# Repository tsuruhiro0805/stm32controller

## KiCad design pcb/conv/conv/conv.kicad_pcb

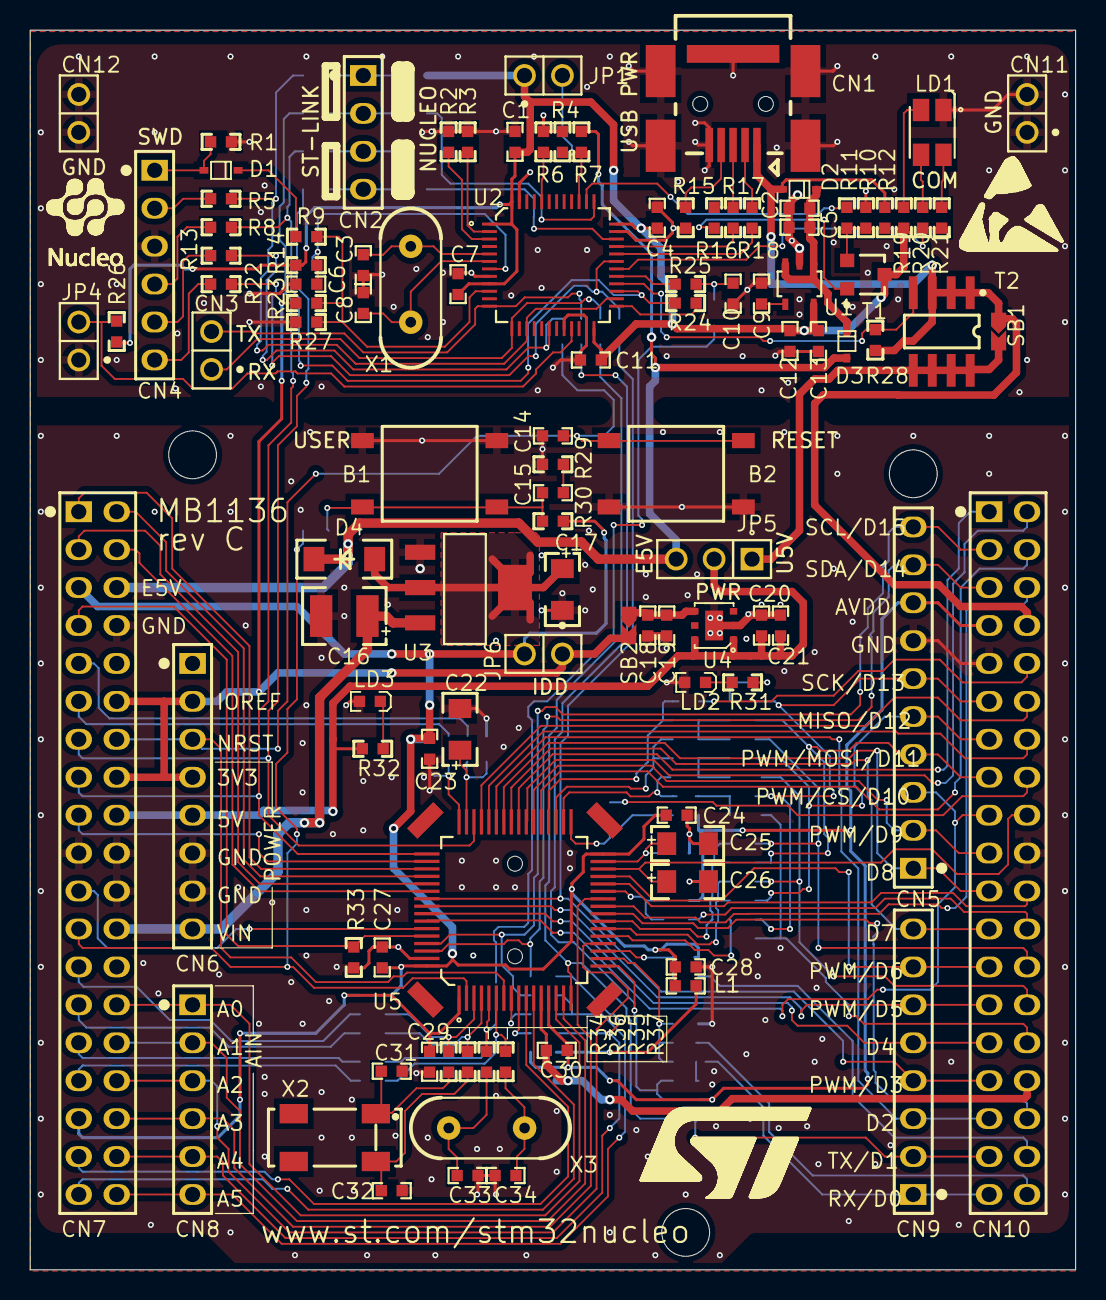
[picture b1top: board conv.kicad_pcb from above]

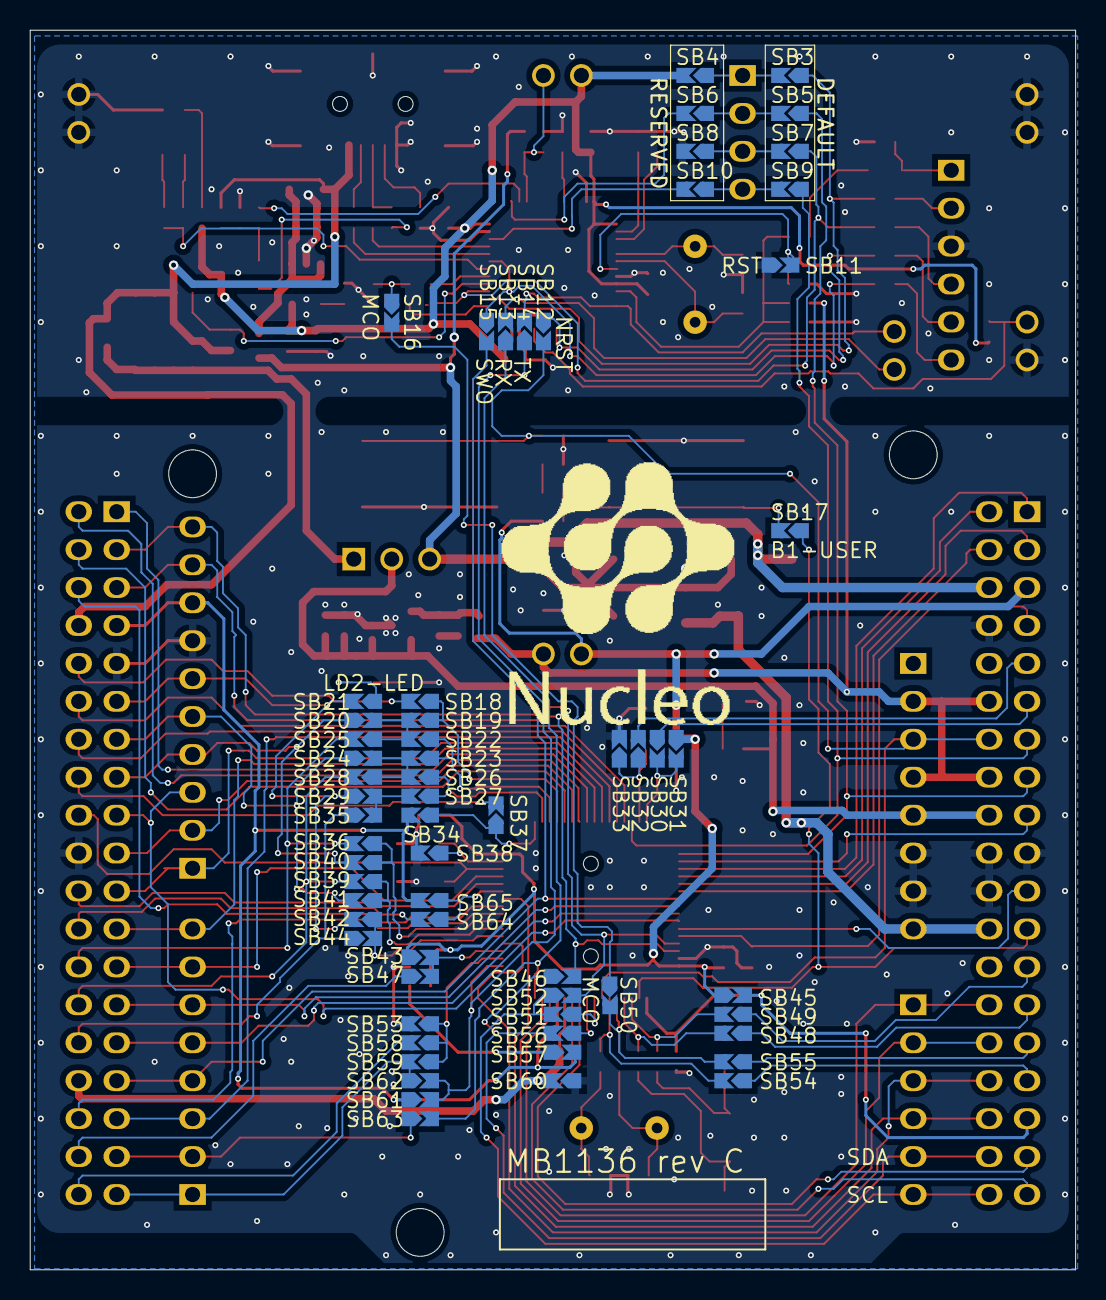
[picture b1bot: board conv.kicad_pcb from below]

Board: 2 copper layers, 70.0 x 83.0 mm, 176 parts (64 on the bottom side), 152 nets.

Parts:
B1: USER (Blue); PB10
B2: TD-0341 [RESET/Black]; PB10
C1, C4, C5, C6, C7, C11, C12, C14, C15, C19, C20, C23, C24, C27, C28, C30: 100nF; 0603C
C2, C13, C18, C21, C29: 1uF_X5R_0603; 0603C
C3, C8, C10: 20pF; 0603C
C9: 10nF_X7R_0603; 0603C
C16: 10uF(25V); TAN-B
C17: 10uF; TAN-A
C22, C25, C26: 2.2uF; TAN-A
C31, C32: 10pF[N/A]; 0603C
C33, C34: 20pF[N/A]; 0603C
CN1: 5075BMR-05-SM; USB-MINI-B-SMD
CN2: Header 4; 1*4
CN3, CN11, CN12: SIP2/2.54
CN4: Header 6X1; 1*6P
CN5: Header 10X1_Female; 1*10P_FEMALE
CN6, CN9: Header 8X1_Female; 1*8P_FEMALE
CN7, CN10: Header 19X2; 2*19P
CN8: Header 6X1_Female; 1*6P_FEMALE
D1, D2, D3: BAT60JFILM; SOD323/A
D4: STPS2L30A; SMA
Designator1: Comment; NUCLEO_black 0.5cm
Designator2: Comment; LOGO ESD
Designator4: Comment; NUCLEO_black 2cm
Designator22: Comment; ST_LOGO_10mm
JP1, JP4, JP6: SIP2/2.54
JP5: SIP3
L1: BEAD; 0603L
LD1: LD_BICOLOR_CMS; HSMF-A201
LD2: Green; 0603D
LD3: RED; 0603D
R1, R2, R3, R12, R26, R33: 10K; 0603R
R4, R23, R27, R28, R30: 4K7; 0603R
R5, R8, R13, R22: 22; 0603R
R6, R14, R15: 100K; 0603R
R7: 2K7; 0603R
R9, R11, R20, R21, R24, R25, R29: 100; 0603R
R10: 36K; 0603R
R16: 1K5; 0603R
R17, R18, R19: 0; 0603R
R31: 510; 0603R
R32: 1K; 0603R
R34, R35, R36, R37: [N/A]; 0603R
SB1, SB2, SB3, SB4, SB5, SB6, SB7, SB8, SB9, SB10, SB11, SB12, SB13, SB14, SB15, SB16, SB17, SB18, SB19, SB20, SB21, SB22, SB23, SB24, SB25, SB26, SB27, SB28, SB29, SB30, SB31, SB32, SB33, SB34, SB35, SB36, SB37, SB38, SB39, SB40, SB41, SB42, SB43, SB44, SB45, SB46, SB47, SB48, SB49, SB50, SB51, SB52, SB53, SB54, SB55, SB56, SB57, SB58, SB59, SB60, SB61, SB62, SB63, SB64, SB65: Circuit Breaker; JP2_SMD
T1: 9013; SOT-23
T2: STS7PF30L; SO8
U1: LD3985M33R; SOT-23-5L
U2: STM32F103CBT6; QFP48 7X7
U3: LD1117S50TR; SOT-223
U4: LD39050PU33R; DFN6(3X3)
U5: MCU_LQFP64; LQFP64
X1: 8MHz(12pF); XTAL1
X2: 32.768K[N/A]; XTAL_4SM_8X3R8
X3: 8MHz(16pF)[N/A]; XTAL1

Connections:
+3V3: CN6.2, CN6.4, CN7.12, CN7.16, JP6.1, R23.1, SB2.2
+3V3_ST_LINK: C1.2, C4.2, C7.2, C11.2, C12.2, C13.1, JP1.1, R14.2, R19.2, R26.1, SB4.2, T1.3, U1.5, U2.1, U2.9, U2.24, U2.36, U2.48
+5V: C20.2, C21.1, CN6.5, CN7.18, JP5.2, R32.2, U4.1, U4.6
AGND: C30.2, CN10.32, SB60.2, U5.12
AIN_1: R9.2, R23.2, R27.2, U2.10
AVDD: C30.1, CN5.8, CN10.7, SB34.2, SB57.2, SB61.1, SB65.2, U5.13
BOOT0: CN7.7, R33.1, U5.60
E5V: CN7.6, D3.1, D4.2, JP5.3, R7.1
GND: B1.1, B1.4, B2.1, B2.4, C1.1, C2.1, C3.2, C4.1, C5.1, C6.1, C7.1, C8.2, C9.1, C10.2, C11.1, C12.1, C13.2, C14.1, C16.2, C17.2, C18.2, C19.1, C20.1, C21.2, C22.2, C23.2, C24.2, C25.2, C26.2, C27.2, C28.2, C29.2, C31.2, C32.2, C33.2, C34.2, CN1.5, CN1.6, CN4.3, CN5.7, CN6.6, CN6.7, CN7.8, CN7.19, CN7.20, CN7.22, CN10.9, CN10.20, CN11.1, CN11.2, CN12.1, CN12.2, JP4.1, LD1.1, LD2.2, LD3.2, R1.2, R2.1, R3.1, R4.2, R6.1, R10.1, R15.2, R27.1, R29.1, R33.2, SB8.2, SB11.1, SB33.2, SB38.2, SB53.2, SB60.1, U1.2, U2.8, U2.20, U2.23, U2.35, U2.47, U3.1, U4.0, U4.2, U5.63
LED_STLINK: R20.1, R21.1, U2.30
MCO: SB16.2, SB50.1
NRST: B2.2, B2.3, C14.2, CN6.3, CN7.14, SB12.2, U5.7
NetB1_2: B1.2, B1.3, C15.2, R30.1, SB17.2
NetC2_2: C2.2, C5.2, D2.2, D3.2, U1.1, U1.3
NetC9_2: C9.2, U1.4
NetC10_1: C10.1, R25.2, SB16.1
NetC15_1: C15.1, R29.2
NetC17_1: C17.1, D4.1, U3.2, U3.4
NetC18_1: C18.1, C19.2, SB2.1, U4.4
NetC22_1: C22.1, SB32.1, SB33.1, U5.47
NetC25_1: C25.1, SB38.1, U5.31
NetC31_1: C31.1, R34.1, X2.1
NetC32_1: C32.1, R36.1, X2.4
NetC33_1: C33.1, R35.2, X3.2
NetC34_1: C34.1, R37.2, X3.1
NetCN1_2: CN1.2, R18.1
NetCN1_3: CN1.3, R16.1, R17.1
NetCN1_4: CN1.4, R15.1
NetCN2_1: CN2.1, SB3.2, SB4.1
NetCN2_2: CN2.2, SB5.2, SB6.1
NetCN2_3: CN2.3, SB7.2, SB8.1
NetCN2_4: CN2.4, SB9.2, SB10.1
NetCN4_1: CN4.1, D1.1, R1.1
NetCN4_2: CN4.2, R5.1
NetCN4_4: CN4.4, R8.1
NetCN4_5: CN4.5, R13.1
NetCN4_6: CN4.6, R22.1
NetCN5_4: CN5.4, CN10.15, SB20.1, SB40.2
NetCN5_5: CN5.5, CN10.13, SB24.1, SB41.2
NetCN5_6: CN5.6, CN10.11, SB21.2, SB29.1, SB42.2
NetCN7_25: CN7.25, SB49.1
NetCN7_27: CN7.27, SB48.1
NetCN7_29: CN7.29, SB55.1
NetCN7_31: CN7.31, SB54.1
NetCN7_36: CN7.36, CN8.5, SB46.1, SB56.2
NetCN7_38: CN7.38, CN8.6, SB51.2, SB52.1
NetCN10_26: CN10.26, SB25.2, SB36.2
NetCN10_28: CN10.28, SB28.2, SB39.2
NetCN10_30: CN10.30, SB35.1, SB44.1
NetD1_2: D1.2, R9.1
NetJP1_2: JP1.2, R4.1, R7.2, U2.39
NetJP4_2: JP4.2, R26.2, U2.21
NetJP5_1: JP5.1, SB1.2, T2.5, T2.6, T2.7, T2.8
NetL1_2: L1.2, SB57.1
NetLD1_2: LD1.2, R21.2
NetLD1_3: LD1.3, R20.2
NetLD1_4: LD1.4, R19.1
NetLD2_1: LD2.1, R31.2
NetLD3_1: LD3.1, R32.1
NetR2_2: R2.2, U2.3
NetR3_2: R3.2, U2.2
NetR6_2: R6.2, U2.44
NetR10_2: R10.2, R11.1, R12.1, T1.2
NetR16_2: R16.2, T1.1
NetR25_1: R25.1, U2.29
NetR28_2: R28.2, T2.4, U2.28
NetR31_1: R31.1, SB21.1
NetSB13_1: SB13.1, SB63.2, U5.16
NetSB14_1: SB14.1, SB61.2, SB62.2, U5.17
NetSB18_1: SB18.1, SB19.1, U5.36
NetSB22_1: SB22.1, SB23.1, U5.35
NetSB26_1: SB26.1, SB27.1, U5.34
NetSB30_2: SB30.2, SB31.2, U5.48
NetSB34_1: SB34.1, SB37.1, U5.33
NetSB43_2: SB43.2, SB47.2, U5.19
NetSB53_1: SB53.1, SB58.1, SB59.1, U5.18
NetSB64_1: SB64.1, SB65.1, U5.27
OSC_IN: C3.1, U2.5, X1.2
OSC_OUT: C8.1, U2.6, X1.1
PA0: CN7.28, CN8.1, U5.14
PA1: CN7.30, CN8.2, U5.15
PA2: CN9.2, CN10.35, SB63.1
PA3: CN9.1, CN10.37, SB59.2, SB62.1
PA4: CN7.32, CN8.3, U5.20
PA5: SB42.1, SB44.2, U5.21
PA6: SB39.1, SB41.1, U5.22
PA7: SB36.1, SB40.1, U5.23
PA8: CN9.8, CN10.23, U5.41
PA9: CN5.1, CN10.21, U5.42
PA10: CN9.3, CN10.33, U5.43
PA11: CN10.14, U5.44
PA12: CN10.12, U5.45
PA13: CN7.13, SB9.1, U5.46
PA14: CN7.15, SB5.1, U5.49
PA15: CN7.17, U5.50
PB0: CN7.34, CN8.4, U5.26
PB1: CN10.24, SB64.2
PB2: CN10.22, U5.28
PB3: CN9.4, CN10.31, SB15.2, U5.55
PB4: CN9.6, CN10.27, U5.56
PB5: CN9.5, CN10.29, U5.57
PB6: CN5.3, CN10.17, U5.58
PB7: CN7.21, U5.59
PB8: CN5.10, CN10.3, SB52.2, U5.61
PB9: CN5.9, CN10.5, SB46.2, U5.62
PB10: CN9.7, CN10.25, U5.29
PB11: C26.1, CN10.18, U5.30
PB12: CN10.16, SB37.2
PB13: SB27.2, SB29.2, SB35.2
PB14: SB23.2, SB24.2, SB26.2, SB28.1
PB15: SB19.2, SB20.2, SB22.2, SB25.1
PC0: SB51.1, U5.8
PC1: SB56.1, U5.9
PC2: CN7.35, U5.10
PC3: CN7.37, U5.11
PC4: CN10.34, U5.24
PC5: CN10.6, U5.25
PC6: CN10.4, U5.37
PC7: CN5.2, CN10.19, U5.38
PC8: CN10.2, U5.39
PC9: CN10.1, U5.40
PC10: CN7.1, U5.51
PC11: CN7.2, U5.52
PC12: CN7.3, U5.53
PC13: CN7.23, SB17.1, U5.2
PC14: R34.2, SB49.2, U5.3
PC15: R36.2, SB48.2, U5.4
PD2: CN7.4, U5.54
PD8: CN10.10, SB18.2
PF0: R35.1, SB50.2, SB55.2, U5.5
PF1: R37.1, SB54.2, U5.6
PF4: CN10.38, SB58.2
PF5: CN10.36, SB47.1
PF6: CN7.9, SB32.2
PF7: CN7.11, SB30.1
STLINK_RX: CN3.1, SB13.2, U2.13
STLINK_TX: CN3.2, SB14.2, U2.12
STM_JTCK: SB6.2, U2.37
STM_JTMS: SB10.2, U2.34
STM_RST: C6.2, R14.1, SB11.2, U2.7
T_JTCK: R5.2, SB3.1, U2.15, U2.26
T_JTMS: R8.2, R24.2, SB7.1, U2.27
T_NRST: R13.2, SB12.1, U2.18
T_SWDIO_IN: R24.1, U2.25
T_SWO: R22.2, SB15.1, U2.31
U5V: CN1.1, CN10.8, D2.1, R12.2, R28.1, SB1.1, T2.1, T2.2, T2.3
USB_CTRL: R11.2, U2.38
USB_DM: R18.2, U2.32
USB_DP: R17.2, U2.33
VBAT/VLCD: C29.1, CN7.33, SB45.2, U5.1
VDD: C23.1, C24.1, C27.1, C28.1, CN7.5, JP6.2, L1.1, R30.2, SB31.1, SB43.1, SB45.1, U5.32, U5.64
VIN: C16.1, CN6.8, CN7.24, U3.3

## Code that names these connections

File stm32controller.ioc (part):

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Mcu.Name=STM32F446R(C-E)Tx
Mcu.Package=LQFP64
Mcu.UserName=STM32F446RETx
PA11.Mode=CAN_Activate
PA11.Signal=CAN1_RX
PA12.Mode=CAN_Activate
PA12.Signal=CAN1_TX
PA13.GPIOParameters=GPIO_Label
PA13.GPIO_Label=TMS
PA13.Mode=Serial_Wire
PA13.Signal=SYS_JTMS-SWDIO
PA14.GPIOParameters=GPIO_Label
PA14.GPIO_Label=TCK
PA14.Mode=Serial_Wire
PA14.Signal=SYS_JTCK-SWCLK
PA2.GPIOParameters=GPIO_Label
PA2.GPIO_Label=USART_TX
PA2.Mode=Asynchronous
PA2.Signal=USART2_TX
PA3.GPIOParameters=GPIO_Label
PA3.GPIO_Label=USART_RX
PA3.Mode=Asynchronous
PA3.Signal=USART2_RX
PA5.GPIOParameters=GPIO_Label
PA5.GPIO_Label=LD2 [Green Led]
PA5.Signal=GPIO_Output
PB3.GPIOParameters=GPIO_Label
PB3.GPIO_Label=SWO
PB3.Signal=SYS_JTDO-SWO
PC13.GPIOParameters=GPIO_Label,GPIO_ModeDefaultEXTI
PC13.GPIO_Label=B1 [Blue PushButton]
PC13.GPIO_ModeDefaultEXTI=GPIO_MODE_IT_FALLING
PC13.Signal=GPXTI13
PC14-OSC32_IN.Mode=LSE-External-Oscillator
PC14-OSC32_IN.Signal=RCC_OSC32_IN
PC15-OSC32_OUT.Mode=LSE-External-Oscillator
PC15-OSC32_OUT.Signal=RCC_OSC32_OUT
PH0-OSC_IN.Mode=HSE-External-Oscillator
PH0-OSC_IN.Signal=RCC_OSC_IN
PH1-OSC_OUT.Mode=HSE-External-Oscillator
PH1-OSC_OUT.Signal=RCC_OSC_OUT
RCC.HSE_VALUE=8000000
RCC.SYSCLKFreq_VALUE=84000000
RCC.SYSCLKSource=RCC_SYSCLKSOURCE_PLLCLK
board=NUCLEO-F446RE
boardIOC=true

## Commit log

2024-11-21 add:env
